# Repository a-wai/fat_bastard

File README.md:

Copyright 2019, Arnaud Ferraris.

This documentation describes Open Hardware and is licensed under the
CERN OHL v.1.2.

You may redistribute and modify this documentation under the terms of the
CERN OHL v.1.2. (http://ohwr.org/cernohl).This documentation is distributed
WITHOUT ANY EXPRESS OR IMPLIED WARRANTY, INCLUDING OF MERCHANTABILITY, 
SATISFACTORY QUALITY AND FITNESS FOR A PARTICULAR PURPOSE.

Please see the CERN OHL v.1.2 for applicable conditions.

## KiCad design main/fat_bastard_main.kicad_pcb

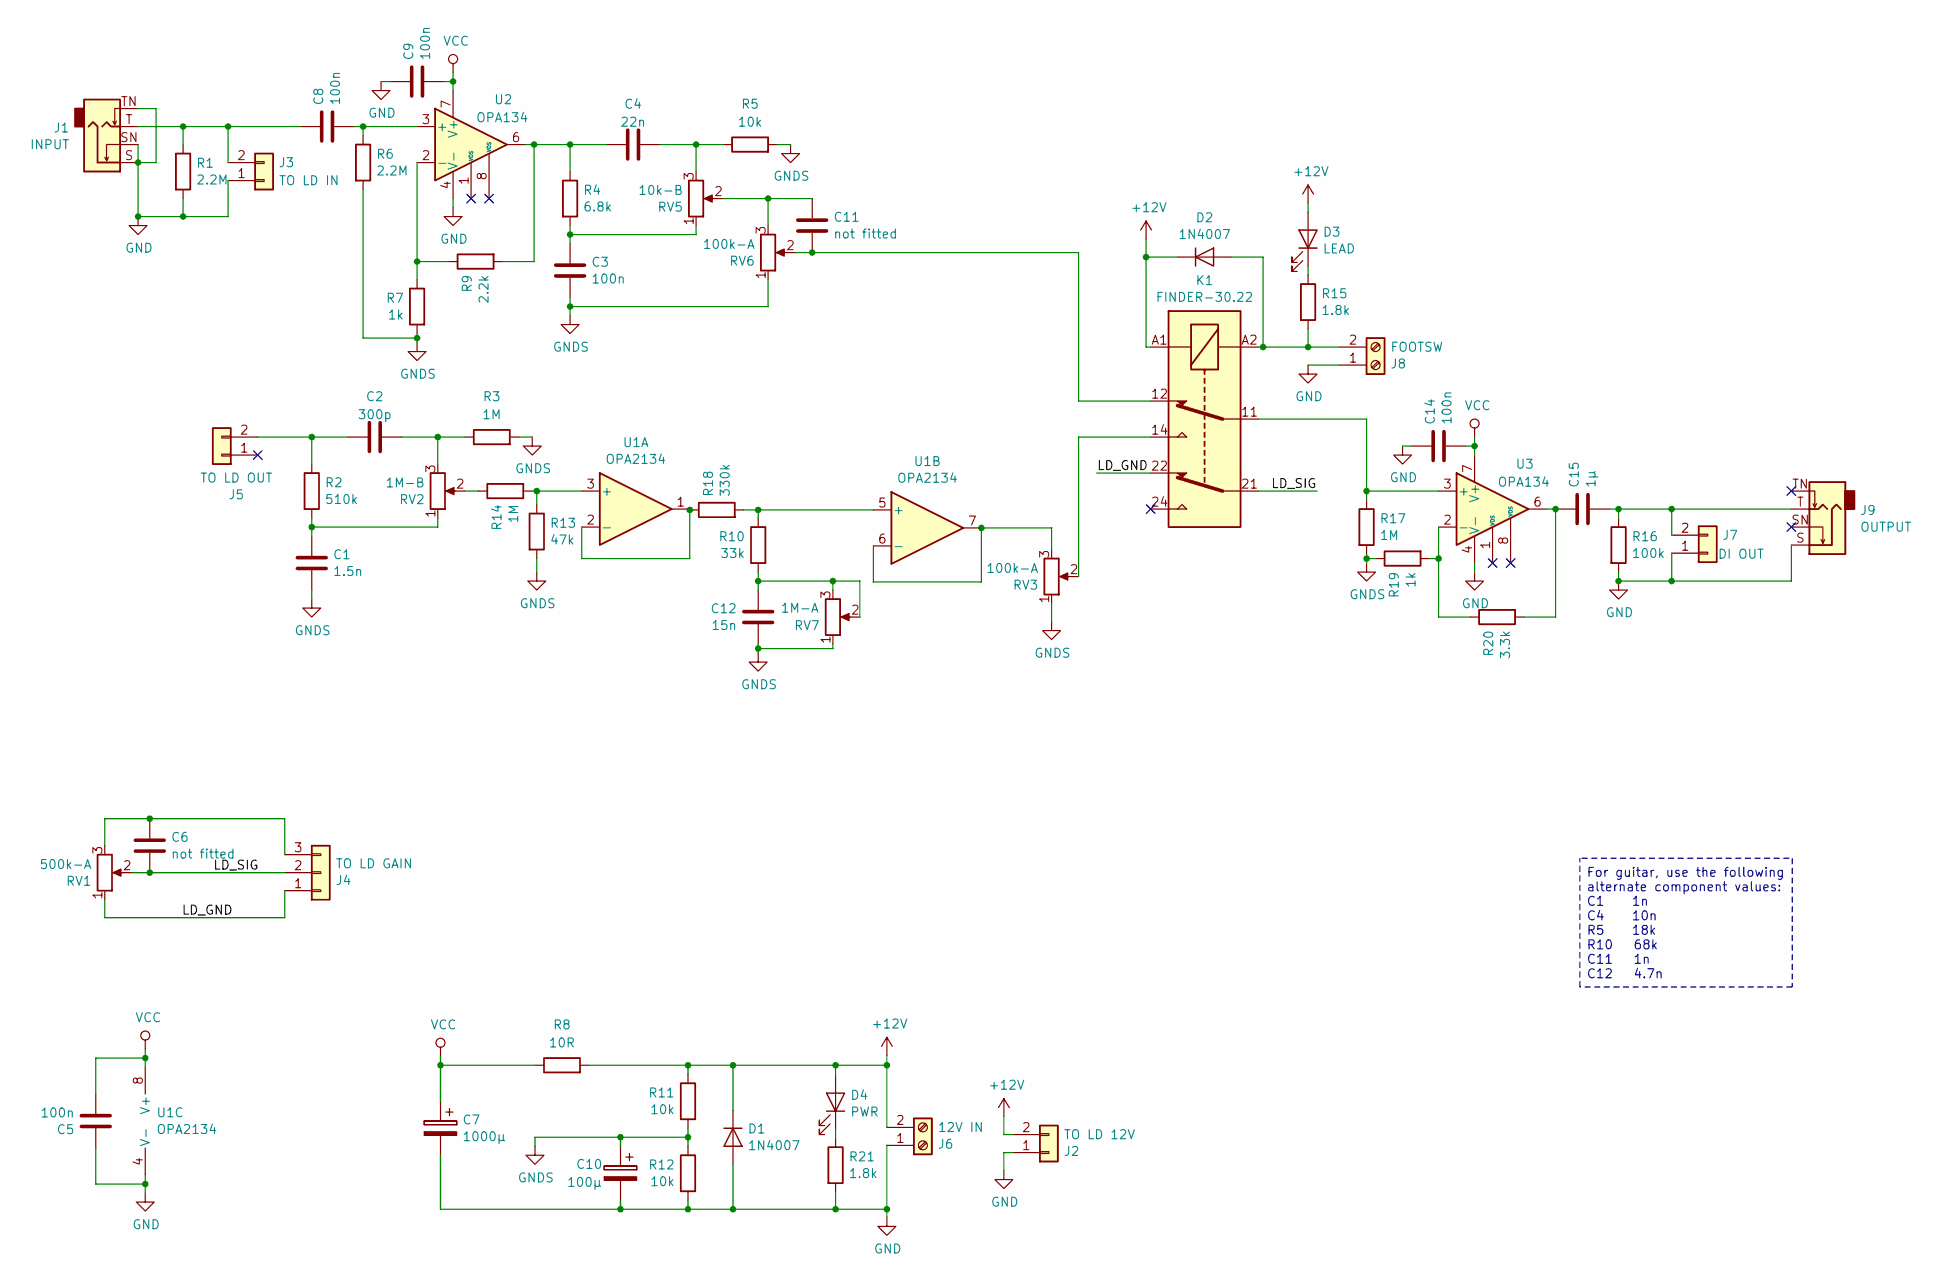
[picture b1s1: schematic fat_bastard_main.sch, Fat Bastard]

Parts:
C1: 1.5n; C_Rect_L7.2mm_W3.0mm_P5.00mm_FKS2_FKP2_MKS2_MKP2; MPN MKP2
C2: 300p; C_Disc_D10.5mm_W5.0mm_P5.00mm
C3, C5, C8, C9, C14: 100n; C_Rect_L7.2mm_W3.0mm_P5.00mm_FKS2_FKP2_MKS2_MKP2; MPN MKS2D031001A00KSSD
C4: 22n; C_Rect_L7.2mm_W3.0mm_P5.00mm_FKS2_FKP2_MKS2_MKP2; MPN MKS2C022201A00KSSD
C6, C11: not fitted; C_Disc_D10.5mm_W5.0mm_P5.00mm
C7: 1000µ; CP_Radial_D10.0mm_P5.00mm
C10: 100µ; CP_Radial_D8.0mm_P3.80mm; MPN FW
C12: 15n; C_Rect_L7.2mm_W3.0mm_P5.00mm_FKS2_FKP2_MKS2_MKP2; MPN MKS2D021001A00KSSD
C15: 1µ; C_Rect_L7.2mm_W4.5mm_P5.00mm_FKS2_FKP2_MKS2_MKP2; MPN MKS2C041001F00KSSD
D1, D2: 1N4007; D_DO-41_SOD81_P7.62mm_Horizontal
D3: LEAD; LED_D3.0mm_Horizontal_O6.35mm_Z10.0mm
D4: PWR; LED_D3.0mm_Horizontal_O3.81mm_Z2.0mm
J1: INPUT; Jack_3.5mm_Neutrik_NMJ6HCD2_Horizontal; MPN NMJ4HCD2
J2: TO LD 12V; PinHeader_1x02_P2.54mm_Vertical
J3: TO LD IN; PinHeader_1x02_P2.54mm_Vertical
J4: TO LD GAIN; PinHeader_1x03_P2.54mm_Vertical
J5: TO LD OUT; PinHeader_1x02_P2.54mm_Vertical
J6: 12V IN; TerminalBlock_RND_205-00001_1x02_P5.00mm_Horizontal; MPN 691102710002
J7: DI OUT; PinHeader_1x02_P2.54mm_Vertical
J8: FOOTSW; TerminalBlock_RND_205-00001_1x02_P5.00mm_Horizontal; MPN 691102710002
J9: OUTPUT; Jack_3.5mm_Neutrik_NMJ6HCD2_Horizontal; MPN NMJ4HCD2
K1: FINDER-30.22; Relay_DPDT_Finder_30.22; MPN G5V-2
R1, R6: 2.2M; R_Axial_DIN0309_L9.0mm_D3.2mm_P12.70mm_Horizontal
R2: 510k; R_Axial_DIN0309_L9.0mm_D3.2mm_P12.70mm_Horizontal
R3, R14, R17: 1M; R_Axial_DIN0309_L9.0mm_D3.2mm_P12.70mm_Horizontal
R4: 6.8k; R_Axial_DIN0309_L9.0mm_D3.2mm_P12.70mm_Horizontal
R5, R11, R12: 10k; R_Axial_DIN0309_L9.0mm_D3.2mm_P12.70mm_Horizontal
R7, R19: 1k; R_Axial_DIN0309_L9.0mm_D3.2mm_P12.70mm_Horizontal
R8: 10R; R_Axial_DIN0309_L9.0mm_D3.2mm_P12.70mm_Horizontal
R9: 2.2k; R_Axial_DIN0309_L9.0mm_D3.2mm_P12.70mm_Horizontal
R10: 33k; R_Axial_DIN0309_L9.0mm_D3.2mm_P12.70mm_Horizontal
R13: 47k; R_Axial_DIN0309_L9.0mm_D3.2mm_P12.70mm_Horizontal
R15, R21: 1.8k; R_Axial_DIN0309_L9.0mm_D3.2mm_P12.70mm_Horizontal
R16: 100k; R_Axial_DIN0309_L9.0mm_D3.2mm_P12.70mm_Horizontal
R18: 330k; R_Axial_DIN0309_L9.0mm_D3.2mm_P12.70mm_Horizontal
R20: 3.3k; R_Axial_DIN0309_L9.0mm_D3.2mm_P12.70mm_Horizontal
RV1: 500k-A; Potentiometer_Alps_RK163_Single_Horizontal
RV2: 1M-B; Potentiometer_Alps_RK163_Single_Horizontal
RV3, RV6: 100k-A; Potentiometer_Alps_RK163_Single_Horizontal
RV5: 10k-B; Potentiometer_Alps_RK163_Single_Horizontal
RV7: 1M-A; Potentiometer_Alps_RK163_Single_Horizontal
U1: OPA2134; DIP-8_W7.62mm_Socket_LongPads; MPN OPA2134PA
U2, U3: OPA134; DIP-8_W7.62mm_Socket_LongPads; MPN OPA134PA

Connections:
+12V: D1.1 (K), D2.1 (K), D3.2 (A), D4.2 (A), J2.2, J6.2, K1.A1, R8.2, R11.1
/LD_GND: J4.1, K1.22, RV1.1
/LD_SIG: C6.1, J4.2, K1.21, RV1.2
GND: C5.2, C7.2, C9.2, C10.2, C14.2, D1.2 (A), J1.S, J1.SN, J1.TN, J2.1, J3.1, J6.1, J7.1, J8.1, J9.S, R1.2, R12.2, R16.2, R21.2, U1.4 (V-), U2.4 (V-), U3.4 (V-)
GNDS: C1.1, C3.1, C10.1, C12.1, R3.2, R5.2, R6.2, R7.2, R11.2, R12.1, R13.2, R17.2, R19.1, RV3.1, RV6.1, RV7.1
unnamed: C1.2, R2.2, RV2.1
unnamed: C2.1, J5.2, R2.1
unnamed: C2.2, R3.1, RV2.3
unnamed: C3.2, R4.2, RV5.1
unnamed: C4.1, R4.1, R9.2, U2.6
unnamed: C4.2, R5.1, RV5.3
unnamed: C6.2, J4.3, RV1.3
unnamed: C8.1, R6.1, U2.3 (+)
unnamed: C8.2, J1.T, J3.2, R1.1
unnamed: C11.1, K1.12, RV6.2
unnamed: C11.2, RV5.2, RV6.3
unnamed: C12.2, R10.2, RV7.2, RV7.3
unnamed: C15.1, J7.2, J9.T, R16.1
unnamed: C15.2, R20.2, U3.6
unnamed: D2.2 (A), J8.2, K1.A2, R15.2
unnamed: D3.1 (K), R15.1
unnamed: D4.1 (K), R21.1
unnamed: K1.11, R17.1, U3.3 (+)
unnamed: K1.14, RV3.2
unnamed: R7.1, R9.1, U2.2 (-)
unnamed: R10.1, R18.2, U1.5 (+)
unnamed: R13.1, R14.2, U1.3 (+)
unnamed: R14.1, RV2.2
unnamed: R18.1, U1.1, U1.2 (-)
unnamed: R19.2, R20.1, U3.2 (-)
unnamed: RV3.3, U1.6 (-), U1.7
VCC: C5.1, C7.1, C9.1, C14.1, R8.1, U1.8 (V+), U2.7 (V+), U3.7 (V+)

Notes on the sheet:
For guitar, use the following alternate component values: C1 1n C4 10n R5 18k R10 68k C11 1n C12 4.7n

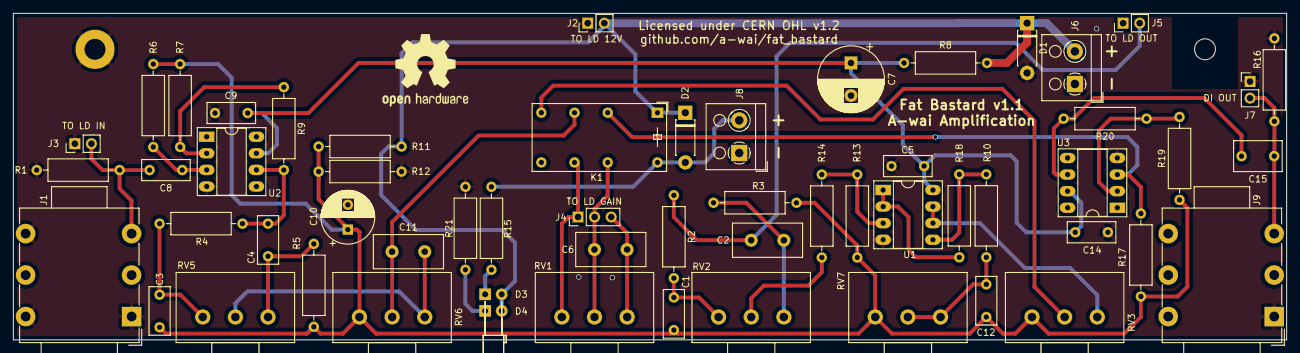
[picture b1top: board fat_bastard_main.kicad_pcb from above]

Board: 2 copper layers, 195.0 x 50.0 mm, 60 parts (0 on the bottom side), 32 nets.

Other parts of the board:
DRILL: MountingHole_3.2mm_M3
DRILL#2: MountingHole_3.2mm_M3

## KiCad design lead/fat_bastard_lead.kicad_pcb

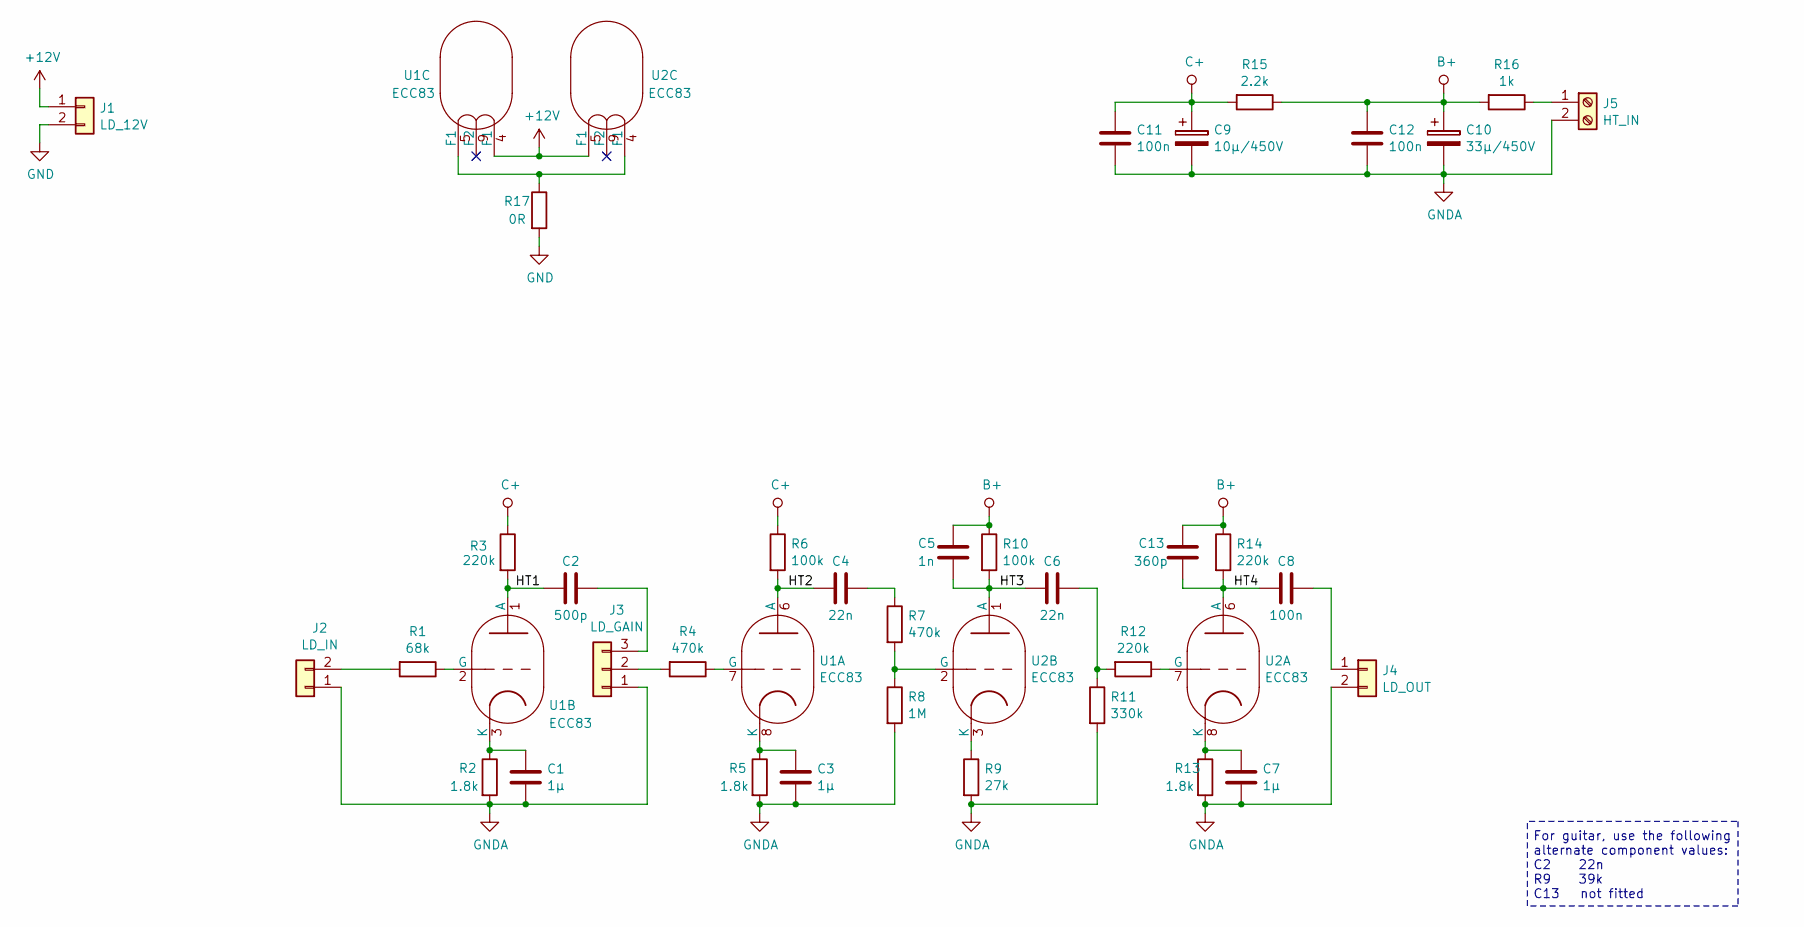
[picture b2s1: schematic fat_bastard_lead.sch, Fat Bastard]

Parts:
C1, C3, C7: 1µ; C_Rect_L7.2mm_W4.5mm_P5.00mm_FKS2_FKP2_MKS2_MKP2
C2: 500p; C_Disc_D11.0mm_W5.0mm_P5.00mm
C4, C6: 22n; C_Rect_L13.0mm_W4.0mm_P10.00mm_FKS3_FKP3_MKS4
C5: 1n; C_Rect_L13.0mm_W4.0mm_P10.00mm_FKS3_FKP3_MKS4
C8, C11, C12: 100n; C_Rect_L19.0mm_W6.0mm_P15.00mm_MKS4
C9: 10µ/450V; CP_Radial_D13.0mm_P5.00mm
C10: 33µ/450V; CP_Radial_D16.0mm_P7.50mm
C13: 360p; C_Disc_D11.0mm_W5.0mm_P5.00mm
J1: LD_12V; PinHeader_1x02_P2.54mm_Horizontal
J2: LD_IN; PinHeader_1x02_P2.54mm_Vertical
J3: LD_GAIN; PinHeader_1x03_P2.54mm_Vertical
J4: LD_OUT; PinHeader_1x02_P2.54mm_Horizontal
J5: HT_IN; TerminalBlock_RND_205-00001_1x02_P5.00mm_Horizontal
R1: 68k; R_Axial_DIN0309_L9.0mm_D3.2mm_P12.70mm_Horizontal
R2, R5, R13: 1.8k; R_Axial_DIN0309_L9.0mm_D3.2mm_P12.70mm_Horizontal
R3, R12, R14: 220k; R_Axial_DIN0309_L9.0mm_D3.2mm_P12.70mm_Horizontal
R4, R7: 470k; R_Axial_DIN0309_L9.0mm_D3.2mm_P12.70mm_Horizontal
R6, R10: 100k; R_Axial_DIN0309_L9.0mm_D3.2mm_P12.70mm_Horizontal
R8: 1M; R_Axial_DIN0309_L9.0mm_D3.2mm_P12.70mm_Horizontal
R9: 27k; R_Axial_DIN0309_L9.0mm_D3.2mm_P12.70mm_Horizontal
R11: 330k; R_Axial_DIN0309_L9.0mm_D3.2mm_P12.70mm_Horizontal
R15: 2.2k; R_Axial_DIN0309_L9.0mm_D3.2mm_P12.70mm_Horizontal
R16: 1k; R_Axial_DIN0309_L9.0mm_D3.2mm_P12.70mm_Horizontal
R17: 0R; SolderJumper-2_P1.3mm_Bridged2Bar_Pad1.0x1.5mm
U1, U2: ECC83; Valve_Noval-B9A_Belton-VT9-PT_Socket

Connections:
+12V: J1.1, U1.4 (F1), U2.5 (F1)
/HT1: C2.2, R3.2, U1.1 (A)
/HT2: C4.2, R6.2, U1.6 (A)
/HT3: C5.2, C6.2, R10.2, U2.1 (A)
/HT4: C8.2, C13.2, R14.2, U2.6 (A)
B+: C5.1, C10.1, C12.2, C13.1, R10.1, R14.1, R15.1, R16.2
C+: C9.1, C11.2, R3.1, R6.1, R15.2
GND: J1.2, R17.2
GNDA: C1.1, C3.1, C7.1, C9.2, C10.2, C11.1, C12.1, J2.1, J3.1, J4.2, J5.2, R2.2, R5.2, R8.2, R9.2, R11.2, R13.2
unnamed: C1.2, R2.1, U1.3 (K)
unnamed: C2.1, J3.3
unnamed: C3.2, R5.1, U1.8 (K)
unnamed: C4.1, R7.1
unnamed: C6.1, R11.1, R12.2
unnamed: C7.2, R13.1, U2.8 (K)
unnamed: C8.1, J4.1
unnamed: J2.2, R1.2
unnamed: J3.2, R4.2
unnamed: J5.1, R16.1
unnamed: R1.1, U1.2 (G)
unnamed: R4.1, U1.7 (G)
unnamed: R7.2, R8.1, U2.2 (G)
unnamed: R9.1, U2.3 (K)
unnamed: R12.1, U2.7 (G)
unnamed: R17.1, U1.5 (F1), U2.4 (F1)

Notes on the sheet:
For guitar, use the following alternate component values: C2 22n R9 39k C13 not fitted

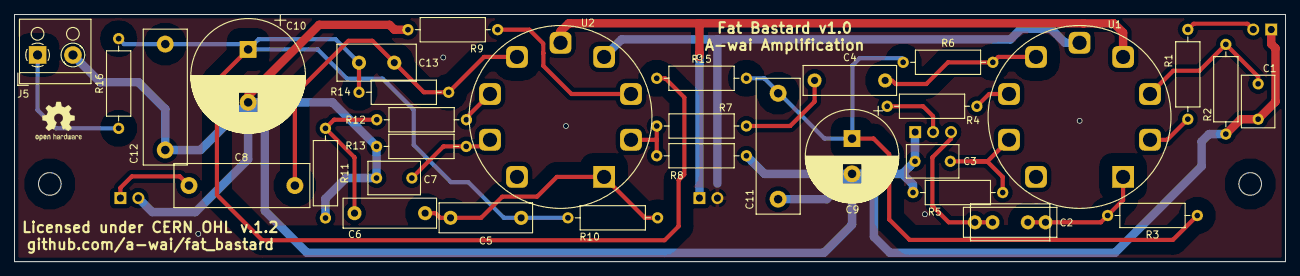
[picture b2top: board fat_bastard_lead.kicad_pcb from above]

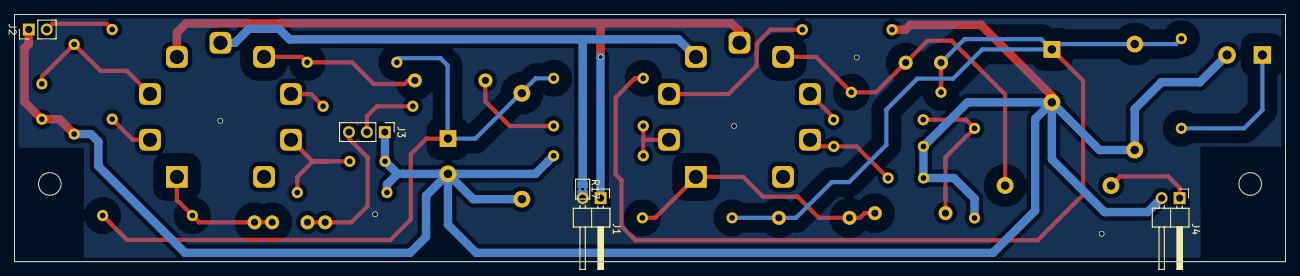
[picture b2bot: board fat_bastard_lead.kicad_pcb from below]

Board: 2 copper layers, 180.0 x 35.0 mm, 39 parts (5 on the bottom side), 25 nets.

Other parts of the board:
DR1, DR1#2: FIX; MountingHole_3.2mm_M3

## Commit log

2019-02-15 Initial release
2019-02-15 Rename file as there will be multiple KiCAD projects/PCBs
    The project will include 2 PCBs: one for the lead channel only, the
    other one for the main circuit. As the files currenly include only the
    lead PCB, rename them to fat_bastard_lead.*
    The main PCB files will be named fat_bastard_main.*
2019-02-15 Route lead channel PCB
2019-02-15 Add main PCB schematic
2019-02-15 Add .gitignore
2019-02-15 Move design files to subdirectories
    In order to keep both PCBs files separate, move all design files to
    lead/ and main/ subfolders.
2019-02-15 Add license (CERN OHL v.1.2)
2019-02-15 Add PDF rendering of the schematics
2019-02-21 Improve tubes PCB & add tubes 3D models
    Small changes were made to the lead PCB in order to avoid having solders
    touching the main PCB.
    Additionnally, the tubes footprints have been replaced to accomodate
    PCB-mount tube sockets, and 3D models have been added for the tubes in
    order to improve 3D rendering.
2019-02-21 Add exclusion zones for mounting brackets
    In order to avoid possible shortcuts, exclusion zones have been added to
    the back side of the PCB, and a few components have been moved in order
    to prevent unwanted contact.
2019-02-21 [main] First version of the main PCB
2019-02-22 [lead] Add small capacitor on last gain stage's anode
    The schematics has too much treble for now, and must be used with the
    Tone setting between 2 and 4/10. Adding this capacitor (300-500p, tune
    to taste) gives a more full-bodied sound, and enables to use the Tone
    control across a broader range.
2019-02-22 [lead] change footprint for C2
    C2 is currently a 500p capacitor, doing heavy filtering of the low
    frequencies to achieve a "modern" tone. By changing the footprint, it
    can be replaced with a film capacitor (i.e. MKS4) of up to 10nF, giving
    a broader range of possible tones.
2019-02-28 [main] Attenuate lead channel & improve buffering + final PCB
    Lead channel has a high output level, while the signal level after the
    Depth control is quite low. Therfore, we need to attenuate the lead
    channel before trying to mix in the signal coming from the Depth pot.
    Additionnally, the output buffer is changed to a make-up gain stage.
    With these changes in mind, the PCB design has been completed.
2019-02-28 [main-alt] Add alternate main PCB
    The Depth control as implemented on the main PCB has been tested to work
    as expected. However, another implementation might be interesting,
    especially when targetting guitar players. This alternate main PCB
    is therefore designed to test another Depth implementation.
2019-03-23 Fix potentiometers orientation
2019-03-23 Improve rounting
2019-03-23 Make main-alt PCB the only main PCB
2019-03-26 Add bright cap, DI out & improve routing
    * Add bright cap on clean channel
    * Add DI out pin header
    * Change connections to improve routing
    * Connect pin 1 of each pin header & terminal block to GND for improved
    consistency
    * Improve overall routing to avoid vias
2019-04-15 [main] Fix channel switching
    Due to changing the schematics layout in the previous version, default
    channel is lead and is muted.
    This commit restores the original layout and fixes the corresponding
    traces.
2019-05-17 Add alternate component values for guitar
    In its original form, this preamp could very well be used with a guitar,
    providing a rather tight and modern sound.
    This patch adds alternate values, designed for use with guitar,
    resulting in a warmer, fuller, stoner/rock guitar tone.
2019-10-02 Add Gerber files

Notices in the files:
lead/fat_bastard_lead.kicad_pcb:
Licensed under CERN OHL v.1.2
